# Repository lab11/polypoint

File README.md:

PolyPoint
=========

PolyPoint is a system for using ultra-wideband RF time-of-flight ranging to perform indoor localization.
It incorporates the DecaWave DW1000 for UWB packet transmission and timestamping
into a solder-on module that provides node-to-node ranges over an I2C interface.

Name
----

The name PolyPoint comes from the use of many polygons and shapes in the prototype design and the
desire to pinpoint where users are with the system.

Git Clone
---------

When cloning this repository, be absolutely sure to do

    git clone --recursive https://github.com/lab11/polypoint.git
    
so that you get the submodules as well. All of the supporting
libraries and build tools are in submodules for the various
hardware platforms used in this project.

Hardware
--------

The PolyPoint system is composed of several hardware pieces. At the core is the
TriPoint module which is a 1.25" on a side triangle that encompasses all of the
core ranging hardware and software. TriPoint has castellated edges and can be
soldered on to a carrier board, effectively as a ranging IC. TriTag is one such
carrier board designed to be the tag in the ranging system. It includes the
UWB antennas and a Bluetooth Low Energy radio plus a battery charging circuit.
TriTag is able to provide ranges to a mobile phone application.

### TriPoint

TriPoint includes the following components:

- DecaWave DW1000 UWB radio
- STM32F031G6U6 MCU
- RF switch

The MCU contains all the necessary code to run the DW1000 and the ranging
protocol.

### TriTag

TriTag includes:

- The TriPoint module
- 3 UWB antennas
- nRF51822 BLE radio
- 3.3 V LDO
- Li-ion battery charger

TriTag is designed to be the tag to be localized in the system and connected
to a smartphone.

### TriDev

TriDev is a breakout and testing board for the TriPoint module.
It contains the same BLE hardware as TriTag, but also adds an FTDI
chip for issuing I2C commands over USB.

Software
--------

PolyPoint contains many software layers that run at various levels of
the system.

#### TriPoint

The core firmware that makes the drop-in TriPoint module work
includes all of the logic to implement two way ToF ranging
on top of the DecaWave DW1000 UWB radio. The firmware architecture
supports multiple "applications", or ranging algorithms, that can
be selected at runtime.

#### TriTag

The TriTag code implements a BLE application
that uses the TriPoint module as an I2C device and prov
a BLE service. It puts the TriTag hardware into TAG mode
and provides ranges over a BLE characteristic. 

#### Phone and BLE

The tools in the `/phone` directory interact with TriTag and read data
across the BLE interface.

----

## Academic Publications

The PolyPoint project has led to two academic publications, and an invited talk at HotWireless'16.
If you are interested in the theory behind the ranging protocol, please check out our publications:

 - **[SurePoint: Exploiting Ultra Wideband Flooding and Diversity to Provide Robust, Scalable, High-Fidelity Indoor Localization.](http://lab11.eecs.berkeley.edu/content/pubs/kempke16surepoint.pdf)** Benjamin Kempke, Pat Pannuto, Bradford Campbell, and Prabal Dutta. Proceedings of the 14th ACM Conference on Embedded Networked Sensor Systems (SenSys’16).
 - **[PolyPoint: Guiding Indoor Quadrotors with Ultra-Wideband Localization.](http://lab11.eecs.berkeley.edu/content/pubs/kempke15polypoint.pdf)** Benjamin Kempke, Pat Pannuto, and Prabal Dutta. 2015 ACM Workshop on Hot Topics in Wireless (HotWireless’15).
 
If you use PolyPoint or its derivatives, please use the following citation:

```bibtex
@inproceedings{kempke16surepoint,
	title = {{SurePoint}: Exploiting Ultra Wideband Flooding and Diversity to Provide Robust, Scalable, High-Fidelity Indoor Localization},
	booktitle = {Proceedings of the 14th ACM Conference on Embedded Networked Sensor Systems},
	series = {SenSys'16},
	year = {2016},
	month = {11},
	location = {Stanford, CA, USA},
	conference-url = {http://sensys.acm.org/2016/},
	author = {Kempke, Benjamin and Pannuto, Pat and Campbell, Bradford and Dutta, Prabal},
}
```

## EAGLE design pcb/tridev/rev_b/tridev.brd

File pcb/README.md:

PolyPoint Hardware
==================

The PolyPoint system consists of several PCBs centered around TriPoint,
the core UWB ranging module.

1. **TriPoint**: Triangular module which contains all necessary hardware
for using the DecaWave DW1000. It has castellated headers so it can be
soldered onto a carrier board to add indoor localization functionality
to any device.

2. **TriTag**: Portable carrier board designed to be used as an indoor
localization tag. Has TriPoint on one side and a BLE radio on the other.

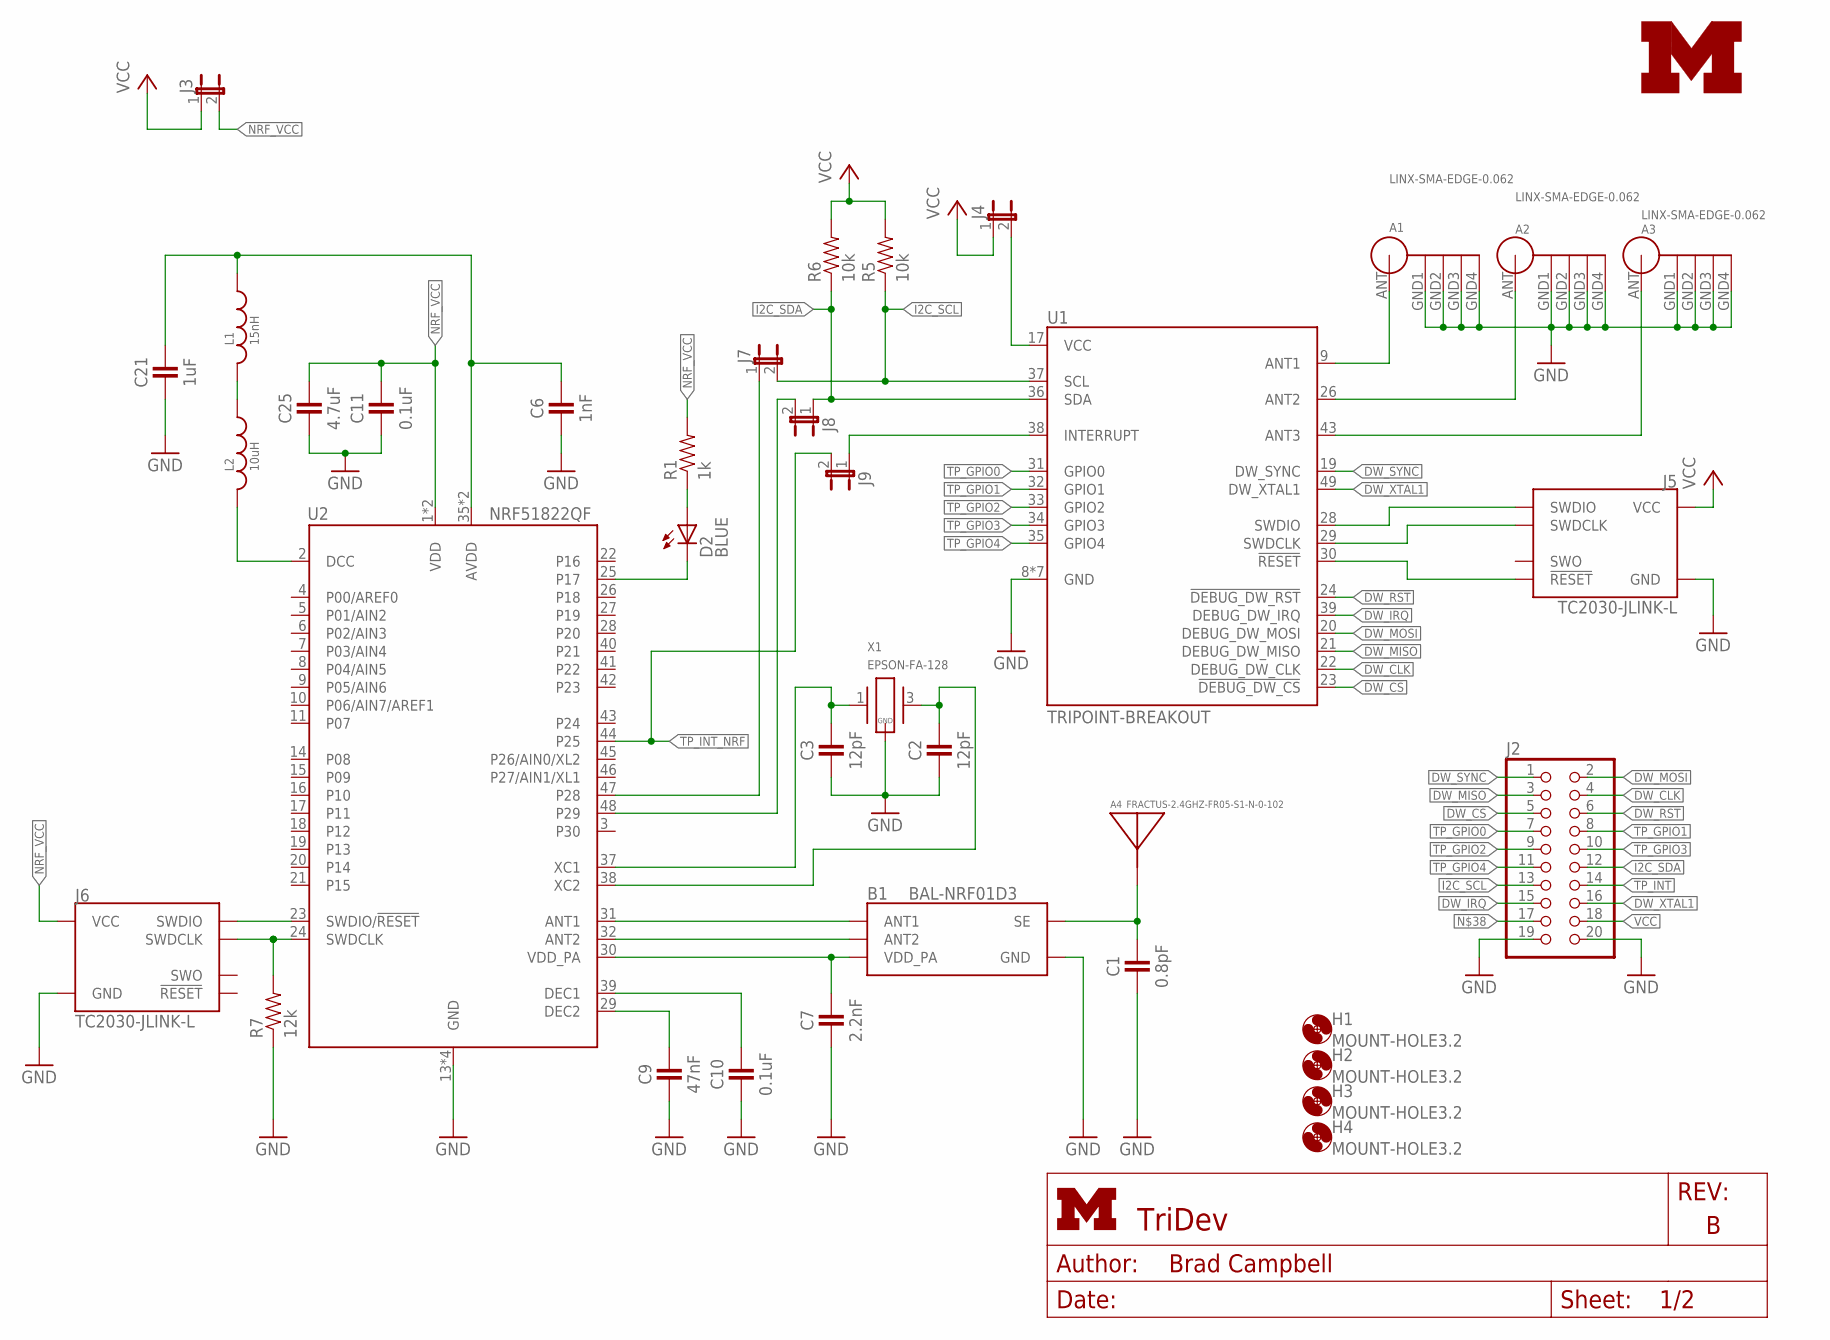
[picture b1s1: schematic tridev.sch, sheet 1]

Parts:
A1, A2, A3: LINX-SMA-EDGE-0.062; CONSMA003.062
A4: FRACTUS-2.4GHZ-FR05-S1-N-0-102; FRACTUS-ANTENNA-FR05-S1-N-0-102
B1: BAL-NRF01D3
C1: 0.8pF; 0402_CAP
C2, C3: 12pF; 0402_CAP
C6: 1nF; 0402_CAP
C7: 2.2nF; 0402_CAP
C9: 47nF; 0402_CAP
C10, C11: 0.1uF; 0402_CAP
C21: 1uF; 0402_CAP
C25: 4.7uF; 0402_CAP
D2: BLUE; LED-0603
H1, H2, H3, H4: MOUNT-HOLE3.2; 3,2
J2: PINHD-2X10; 2X10
J3, J4, J7, J8, J9: JUMPER-2PTH; 1X02
J5, J6: TC2030-JLINK-L; TC2030-IDC
L1: 15nH; 0402_CAP
L2: 10uH; 0603_CAP
LOGO1: UMICH_SOLID_SMALL; UMICH_SOLID_75MIL
R1: 1k; 0402_RES
R5, R6: 10k; 0402_RES
R7: 12k; 0402_RES
U1: TRIPOINT-BREAKOUT
U2: NRF51822QF; QFN-48-6MM
X1: EPSON-FA-128; FA-128

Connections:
!CHRG1: D2.A, R1.1
!DW_CS: J2.5, U1.23 (!DEBUG_DW_CS)
!DW_RST: J2.6, U1.24 (!DEBUG_DW_RST)
ANTENNA: A4.1, B1.SE, C1.1
AVDD: C6.1, C21.1, L1.1, U2.35 (AVDD), U2.36 (AVDD)
DCC: L2.2, U2.2 (DCC)
DW_CLK: J2.4, U1.22 (DEBUG_DW_CLK)
DW_IRQ: J2.15, U1.39 (DEBUG_DW_IRQ)
DW_MISO: J2.3, U1.21 (DEBUG_DW_MISO)
DW_MOSI: J2.2, U1.20 (DEBUG_DW_MOSI)
DW_SYNC: J2.1, U1.19 (DW_SYNC)
DW_XTAL1: J2.16, U1.49 (DW_XTAL1)
GND: A1.GND1, A1.GND2, A1.GND3, A1.GND4, A2.GND1, A2.GND2, A2.GND3, A2.GND4, A3.GND1, A3.GND2, A3.GND3, A3.GND4, B1.GND, C1.2, C2.2, C3.2, C6.2, C7.2, C9.2, C10.2, C11.2, C21.2, C25.2, J2.19, J2.20, J5.5 (GND), J6.5 (GND), R7.1, U1.8 (GND), U1.10 (GND), U1.18 (GND), U1.25 (GND), U1.27 (GND), U1.42 (GND), U1.44 (GND), U2.13 (GND), U2.33 (GND), U2.34 (GND), U2.GND, X1.2 (GND), X1.4 (GND); also elsewhere on the board
I2C_SCL: J2.13, J7.2, R5.1, U1.37 (SCL); also elsewhere on the board
I2C_SCL_NRF: J7.1, U2.47 (P28)
I2C_SDA: J2.12, J8.1, R6.1, U1.36 (SDA); also elsewhere on the board
I2C_SDA_NRF: J8.2, U2.48 (P29)
unnamed: A1.ANT, U1.9 (ANT1)
unnamed: A2.ANT, U1.26 (ANT2)
unnamed: A3.ANT, U1.43 (ANT3)
unnamed: J5.2 (SWDIO), U1.28 (SWDIO)
unnamed: D2.C, U2.25 (P17)
unnamed: J5.4 (SWDCLK), U1.29 (SWDCLK)
unnamed: J5.3 (!RESET), U1.30 (!RESET)
unnamed: C3.1, U2.37 (XC1), X1.1
unnamed: C2.1, U2.38 (XC2), X1.3 (2)
unnamed: C9.1, U2.29 (DEC2)
unnamed: C10.1, U2.39 (DEC1)
unnamed: B1.ANT1, U2.31 (ANT1)
unnamed: B1.ANT2, U2.32 (ANT2)
unnamed: B1.VCC (VDD_PA), C7.1, U2.30 (VDD_PA)
unnamed: J4.2, U1.17 (VCC)
unnamed: L1.2, L2.1
NRF_VCC: C11.1, C25.1, J3.2, J6.1 (VCC), R1.2, U2.1 (VDD), U2.12 (VDD)
SWDCLK: J6.4 (SWDCLK), R7.2, U2.24 (SWDCLK)
SWDIO/!RESET: J6.2 (SWDIO), U2.23 (SWDIO/!RESET)
TP_GPIO0: J2.7, U1.31 (GPIO0)
TP_GPIO1: J2.8, U1.32 (GPIO1)
TP_GPIO2: J2.9, U1.33 (GPIO2)
TP_GPIO3: J2.10, U1.34 (GPIO3)
TP_GPIO4: J2.11, U1.35 (GPIO4)
TP_INT: J2.14, J9.1, U1.38 (INTERRUPT); also elsewhere on the board
TP_INT_NRF: J9.2, U2.44 (P25)
VCC: J2.18, J3.1, J4.1, J5.1 (VCC), R5.2, R6.2; also elsewhere on the board

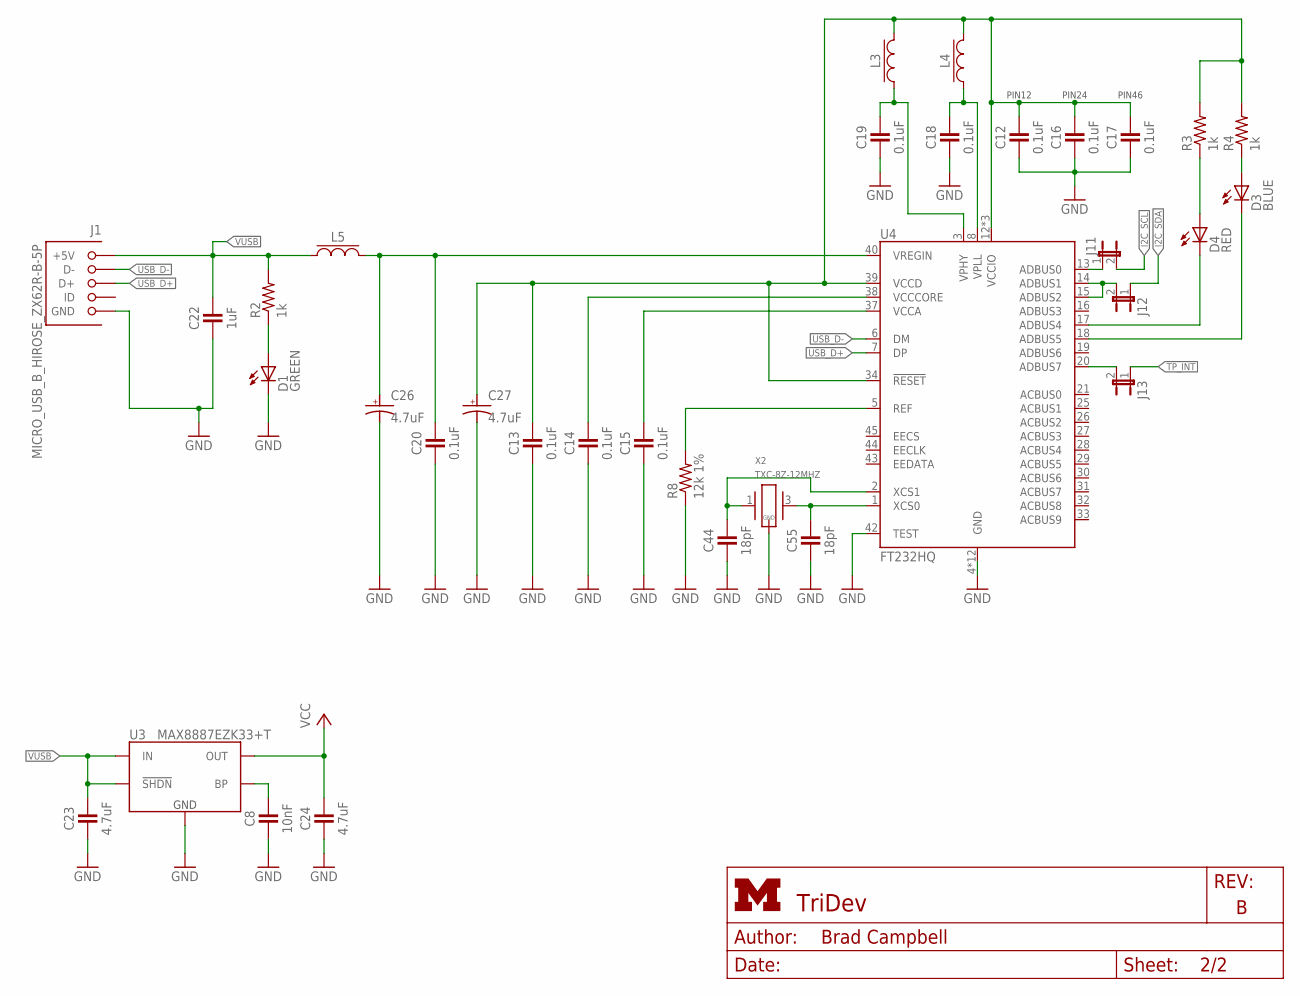
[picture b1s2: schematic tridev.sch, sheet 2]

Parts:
C8: 10nF; 0402_CAP
C12, C13, C14, C15, C16, C17, C18, C19, C20: 0.1uF; 0402_CAP
C22: 1uF; 0402_CAP
C23, C24: 4.7uF; 0402_CAP
C26, C27: 4.7uF; CAP0603; DIGIKEY 478-8656-1-ND
C44, C55: 18pF; 0402_CAP
D1: GREEN; LED-0603
D3: BLUE; LED-0603
D4: RED; LED-0603
J1: MICRO_USB_B_HIROSE_ZX62R-B-5P; USB_MICRO_B-HIROSE-ZX62R-B-5P; MOUSER 798-ZX62R-B-5P
J11, J12, J13: JUMPER-2PTH; 1X02
L3, L4, L5: FERRITE_BEAD; 0603_CAP; DIGIKEY 445-2166-1-ND
R2, R3, R4: 1k; 0402_RES
R8: 12k 1%; 0402_RES
U3: MAX8887EZK33+T; SOT-23-5
U4: FT232HQ; QFN-48-8MM
X2: TXC-8Z-12MHZ; TXC-8Z

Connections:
!CHRG: D1.A, R2.1
GND: C8.2, C12.2, C13.2, C14.2, C15.2, C16.2, C17.2, C18.2, C19.2, C20.2, C22.2, C23.2, C24.2, C26.NEG (ANODE), C27.NEG (ANODE), C44.2, C55.2, D1.C, J1.5 (GND), R8.1, U3.2 (GND), U4.4 (GND), U4.9 (GND), U4.10 (GND), U4.11 (GND), U4.22 (GND), U4.23 (GND), U4.35 (GND), U4.36 (GND), U4.41 (GND), U4.42 (TEST), U4.47 (GND), U4.48 (GND), U4.PAD (GND), X2.2 (GND), X2.4 (GND); also elsewhere on the board
I2C_SCL: J11.2; also elsewhere on the board
I2C_SCL_FTDI: J11.1, U4.13 (ADBUS0)
I2C_SDA: J12.1; also elsewhere on the board
I2C_SDA_FTDI: J12.2, U4.14 (ADBUS1), U4.15 (ADBUS2)
unnamed: D4.C, U4.17 (ADBUS4)
unnamed: C8.1, U3.4 (BP)
unnamed: C20.1, C26.POS (CATHODE), L5.2, U4.40 (VREGIN)
unnamed: C14.1, U4.38 (VCCCORE)
unnamed: C55.1, U4.1 (XCS0), X2.3 (2)
unnamed: C44.1, U4.2 (XCS1), X2.1
unnamed: C15.1, U4.37 (VCCA)
unnamed: R8.2, U4.5 (REF)
unnamed: D4.A, R3.1
unnamed: D3.A, R4.1
unnamed: D3.C, U4.18 (ADBUS5)
TP_INT: J13.1; also elsewhere on the board
TP_INT_FTDI: J13.2, U4.20 (ADBUS7)
USB_D+: J1.3 (D+), U4.7 (DP)
USB_D-: J1.2 (D-), U4.6 (DM)
VCC: C24.1, U3.5 (OUT); also elsewhere on the board
VCC3V3: C12.1, C13.1, C16.1, C17.1, C27.POS (CATHODE), L3.2, L4.2, R3.2, R4.2, U4.12 (VCCIO), U4.24 (VCCIO), U4.34 (!RESET), U4.39 (VCCD), U4.46 (VCCIO)
VPHY: C19.1, L3.1, U4.3 (VPHY)
VPLL: C18.1, L4.1, U4.8 (VPLL)
VUSB: C22.1, C23.1, J1.1 (+5V), L5.1, R2.2, U3.1 (IN), U3.3 (!SHDN)

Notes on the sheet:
PIN12
PIN24
PIN46

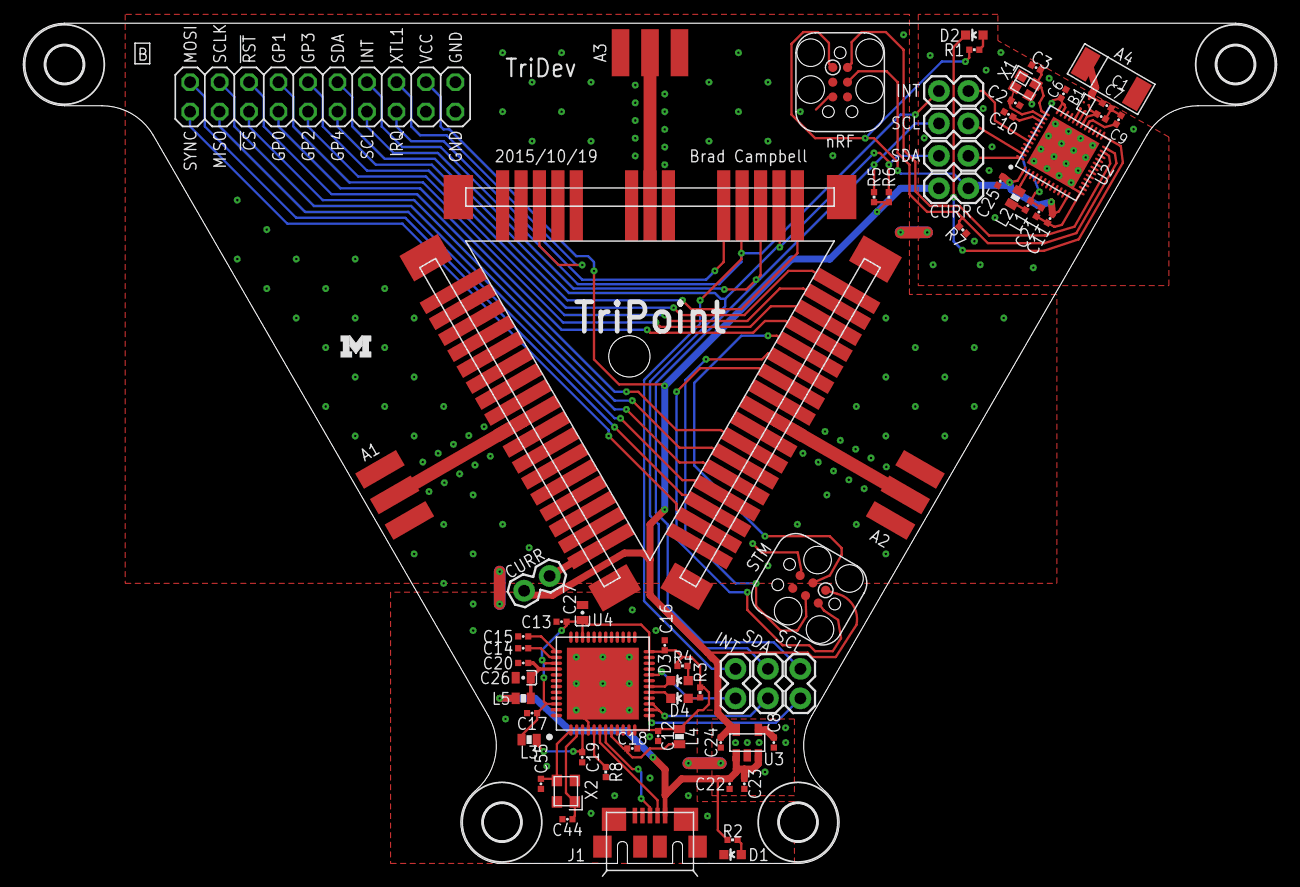
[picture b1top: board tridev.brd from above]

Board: 2 copper layers, 108.0 x 72.4 mm, 72 parts (0 on the bottom side), 65 nets.

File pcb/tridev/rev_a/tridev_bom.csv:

Qty,Value,Device,Package,Parts,Description,DIGIKEY,MOUSER,NEWARK,RICHARDSON_RFPD,
3,LINX-SMA-EDGE-0.062,LINX-SMA-EDGE-0.062,CONSMA003.062,"A1, A2, A3",CONN SMA JACK 50 OHM EDGE MNT,CONSMA003.062-ND,,,,y
1,FRACTUS-2.4GHZ-FR05-S1-N-0-102,FRACTUS-2.4GHZ-FR05-S1-N-0-102,FRACTUS-ANTENNA-FR05-S1-N-0-102,A4,"Fractus Compact Reach XtendTM chip antenna is engineered specifically for Bluetooth,",,,,FR05-S1-N-0102B,y
1,BAL-NRF01D3,BAL-NRF01D3,BAL-NRF01D3,B1,"50 ohm nominal input / conjugate match balun to nRF51422-QFAA,",497-13637-1-ND,511-BAL-NRF01D3,,,y
1,0.8pF,CAPACITOR,0402_CAP,C1,0402 Capacitor,490-6269-1-ND,,,,y
2,12pF,CAPACITOR,0402_CAP,"C2, C3",0402 Capacitor,490-6197-1-ND,,,,y
2,18pF,CAPACITOR,0402_CAP,"C4, C5",0402 Capacitor,490-6203-1-ND,,,,y
1,1nF,CAPACITOR,0402_CAP,C6,0402 Capacitor,490-1303-1-ND,,,,y
1,2.2nF,CAPACITOR,0402_CAP,C7,0402 Capacitor,490-5419-1-ND,,,,y
1,10nF,CAPACITOR,0402_CAP,C8,0402 Capacitor,445-1260-1-ND,,,,y
1,47nF,CAPACITOR,0402_CAP,C9,0402 Capacitor,445-1264-1-ND,,,,y
11,0.1uF,CAPACITOR,0402_CAP,C10-C20,0402 Capacitor,490-1318-1-ND,,,,y
2,1uF,CAPACITOR,0402_CAP,"C21, C22",0402 Capacitor,445-4998-1-ND,,,,y
3,4.7uF,CAPACITOR,0402_CAP,"C23, C24, C25",0402 Capacitor,445-5947-1-ND,,,,y
2,4.7uF,CAP_POL0603,CAP0603,"C26, C27",0603 Capacitor,478-8656-1-ND,,,,y
1,GREEN,LED0603,LED-0603,D1,LEDs,160-1446-1-ND,,,,y
2,BLUE,LED0603,LED-0603,"D2, D3",LEDs,160-1837-1-ND,,,,y
1,RED,LED0603,LED-0603,D4,LEDs,160-1835-1-ND,,,,y
1,MICRO_USB_B_HIROSE_ZX62R-B-5P,MICRO_USB_B_HIROSE_ZX62R-B-5P,USB_MICRO_B-HIROSE-ZX62R-B-5P,J1,USB Micro B Connector,H11574CT-ND,798-ZX62R-B-5P,69W0714,,y
1,,PINHD-2X10,2X10,J2,PIN HEADER,609-3365-ND,,,,y
2,,JUMPER-2PTH,1X02,"J3, J4",Jumper,,,,,y
1,15nH,INDUCTOR0402,0402_CAP,L1,,587-1521-1-ND,,,,y
1,10uH,INDUCTOR0603,0603_CAP,L2,,490-4025-1-ND,,,,y
3,FERRITE_BEAD,FERRITE_BEAD,0603_CAP,"L3, L4, L5",,445-2166-1-ND,,,,y
4,1k,RESISTOR0402_RES,0402_RES,"R1, R2, R3, R4",Resistor,RHM1.0KCECT-ND,,,,y
2,10k,RESISTOR0402_RES,0402_RES,"R5, R6",Resistor,RHM10.0KCDCT-ND,,,,y
1,12k 1%,RESISTOR0402_RES,0402_RES,"R7, R8",Resistor,RHM12.0KCDCT-ND,,,,y
1,TRIPOINT-BREAKOUT,TRIPOINT-BREAKOUT,TRIPOINT-BREAKOUT,U1,UWB Ranging Module,,,,,y
1,NRF51822QF,NRF51822QF,QFN-48-6MM,U2,Multiprotocol Bluetooth® 4.0 low energy/2.4 GHz RF SoC,1490-1032-1-ND,949-NRF51822-QFAB-R7,,,y
1,MAX8887EZK33+T,MAX8887EZK33+T,SOT-23-5,U3,IC REG LDO 3.3V 0.3A TSOT23-5,MAX8887EZK33+TCT-ND,,,,y
1,FT232HQ,FT232HQ,QFN-48-8MM,U4,Single Channel USB to Multipurpose I/O IC,768-1102-1-ND,895-FT232HQ-REEL,65W8039,,y
1,16MHz,TXC-8Y,TXC-8Y,X1,CRYSTAL 16MHZ 8PF SMD,887-2003-1-ND,,,,y
1,TXC-8Z-12MHZ,TXC-8Z-12MHZ,TXC-8Z,X2,,887-1487-1-ND,,,,y

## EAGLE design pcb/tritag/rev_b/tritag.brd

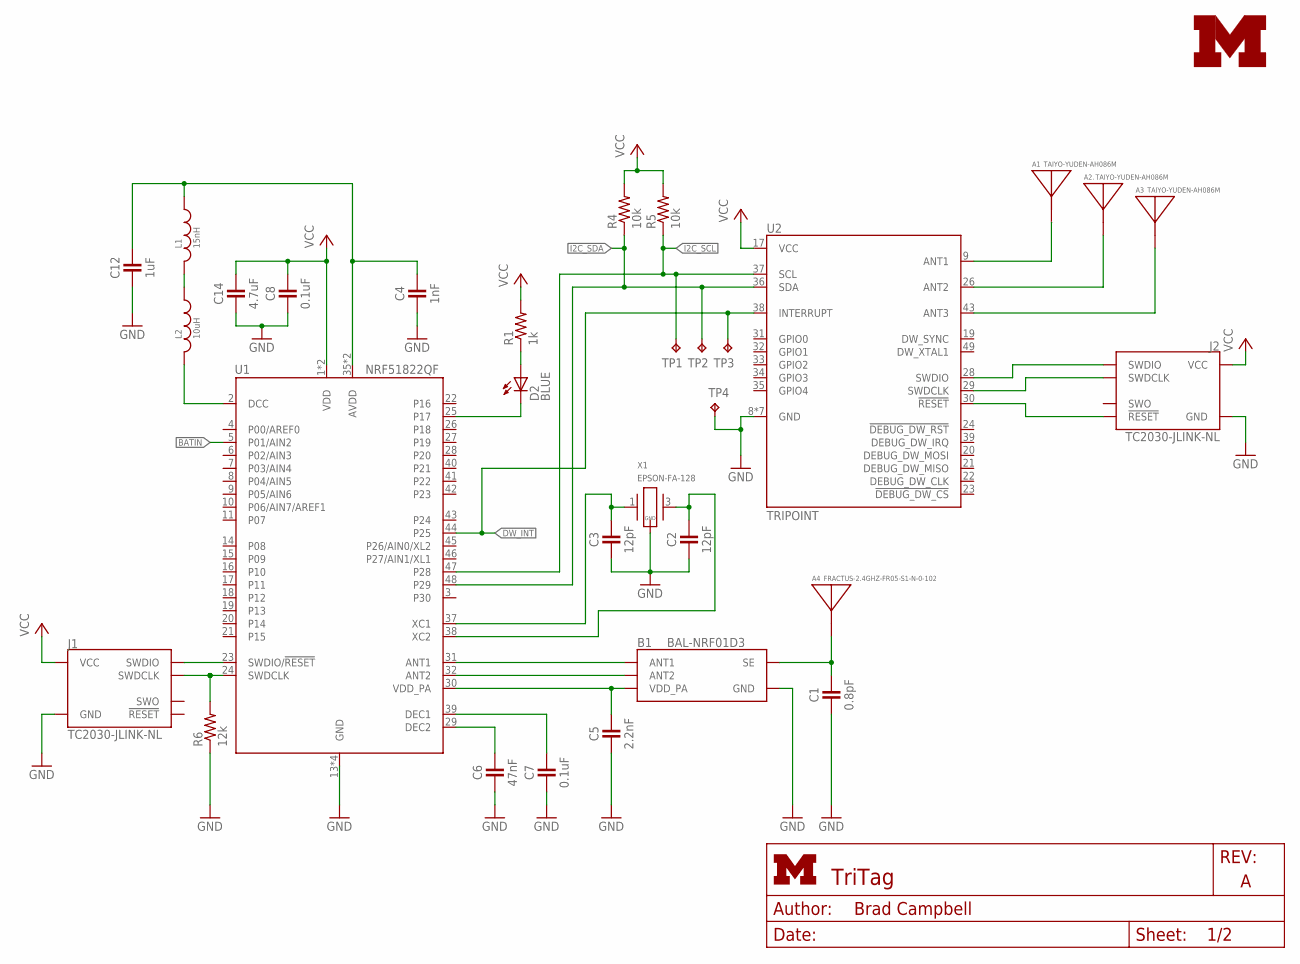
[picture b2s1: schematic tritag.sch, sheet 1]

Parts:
A1, A2., A3: TAIYO-YUDEN-AH086M
A4: FRACTUS-2.4GHZ-FR05-S1-N-0-102; FRACTUS-ANTENNA-FR05-S1-N-0-102
B1: BAL-NRF01D3
C1: 0.8pF; 0402_CAP
C2, C3: 12pF; 0402_CAP
C4: 1nF; 0402_CAP
C5: 2.2nF; 0402_CAP
C6: 47nF; 0402_CAP
C7, C8: 0.1uF; 0402_CAP
C12: 1uF; 0402_CAP
C14: 4.7uF; 0402_CAP
D2: BLUE; LED-0603
J1, J2: TC2030-JLINK-NL; TC2030-IDC-NL
L1: 15nH; 0402_CAP
L2: 10uH; 0603_CAP
LOGO1: UMICH_SOLID_SMALL; UMICH_SOLID_75MIL
R1: 1k; 0402_RES
R4, R5: 10k; 0402_RES
R6: 12k; 0402_RES
TP1, TP2, TP3, TP4: TPTP06SQ; TP06SQ
U1: NRF51822QF; QFN-48-6MM
U2: TRIPOINT
X1: EPSON-FA-128; FA-128

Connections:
!CHRG1: D2.A, R1.1
ANTENNA: A4.1, B1.SE, C1.1
AVDD: C4.1, C12.1, L1.1, U1.35 (AVDD), U1.36 (AVDD)
BATIN: U1.5 (P01/AIN2); also elsewhere on the board
DCC: L2.2, U1.2 (DCC)
DW_INT: TP3.TP, U1.44 (P25), U2.38 (INTERRUPT)
GND: B1.GND, C1.2, C2.2, C3.2, C4.2, C5.2, C6.2, C7.2, C8.2, C12.2, C14.2, J1.5 (GND), J2.5 (GND), R6.1, TP4.TP, U1.13 (GND), U1.33 (GND), U1.34 (GND), U1.GND, U2.8 (GND), U2.10 (GND), U2.18 (GND), U2.25 (GND), U2.27 (GND), U2.42 (GND), U2.44 (GND), X1.2 (GND), X1.4 (GND); also elsewhere on the board
I2C_SCL: R5.1, TP1.TP, U1.47 (P28), U2.37 (SCL)
I2C_SDA: R4.1, TP2.TP, U1.48 (P29), U2.36 (SDA)
unnamed: A1.A, U2.9 (ANT1)
unnamed: A2..A, U2.26 (ANT2)
unnamed: A3.A, U2.43 (ANT3)
unnamed: J2.2 (SWDIO), U2.28 (SWDIO)
unnamed: D2.C, U1.25 (P17)
unnamed: J2.4 (SWDCLK), U2.29 (SWDCLK)
unnamed: J2.3 (!RESET), U2.30 (!RESET)
unnamed: C3.1, U1.37 (XC1), X1.1
unnamed: C2.1, U1.38 (XC2), X1.3 (2)
unnamed: C6.1, U1.29 (DEC2)
unnamed: C7.1, U1.39 (DEC1)
unnamed: B1.ANT1, U1.31 (ANT1)
unnamed: B1.ANT2, U1.32 (ANT2)
unnamed: B1.VCC (VDD_PA), C5.1, U1.30 (VDD_PA)
unnamed: L1.2, L2.1
SWDCLK: J1.4 (SWDCLK), R6.2, U1.24 (SWDCLK)
SWDIO/!RESET: J1.2 (SWDIO), U1.23 (SWDIO/!RESET)
VCC: C8.1, C14.1, J1.1 (VCC), J2.1 (VCC), R1.2, R4.2, R5.2, U1.1 (VDD), U1.12 (VDD), U2.17 (VCC); also elsewhere on the board

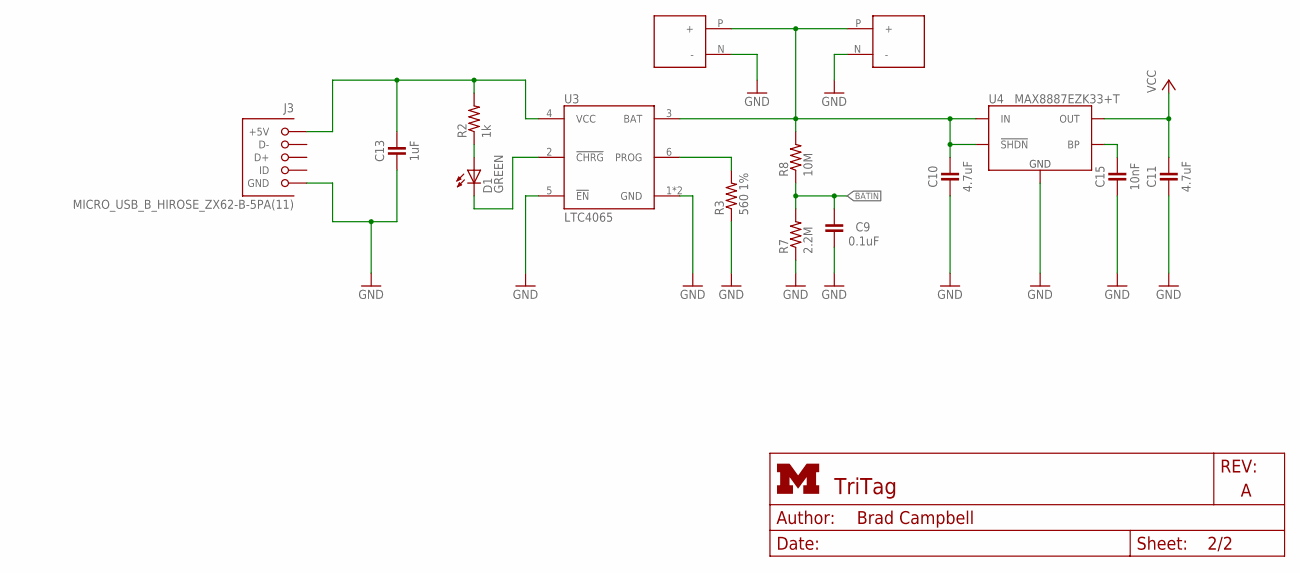
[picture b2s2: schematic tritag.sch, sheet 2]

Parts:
C9: 0.1uF; 0402_CAP
C10, C11: 4.7uF; 0402_CAP
C13: 1uF; 0402_CAP
C15: 10nF; 0402_CAP
D1: GREEN; LED-0603
J3: MICRO_USB_B_HIROSE_ZX62-B-5PA(11); USB_MICRO_B-HIROSE-ZX62-B-5PA(11)
J4, J5: BAT_HOLE; BATTERY_HOLE
R2: 1k; 0402_RES
R3: 560 1%; 0402_RES
R7: 2.2M; 0402_RES
R8: 10M; 0402_RES
U3: LTC4065; DFN-6/2MM
U4: MAX8887EZK33+T; SOT-23-5

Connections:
!CHRG: D1.A, R2.1
BATIN: C9.2, R7.2, R8.1; also elsewhere on the board
GND: C9.1, C10.2, C11.2, C13.2, C15.2, J3.5 (GND), J4.N (-), J5.N (-), R3.1, R7.1, U3.1 (GND), U3.5 (!EN), U3.7 (GND), U4.2 (GND); also elsewhere on the board
unnamed: D1.C, U3.2 (!CHRG)
unnamed: C15.1, U4.4 (BP)
unnamed: R3.2, U3.6 (PROG)
VBAT: C10.1, J4.P (+), J5.P (+), R8.2, U3.3 (BAT), U4.1 (IN), U4.3 (!SHDN)
VCC: C11.1, U4.5 (OUT); also elsewhere on the board
VUSB: C13.1, J3.1 (+5V), R2.2, U3.4 (VCC)

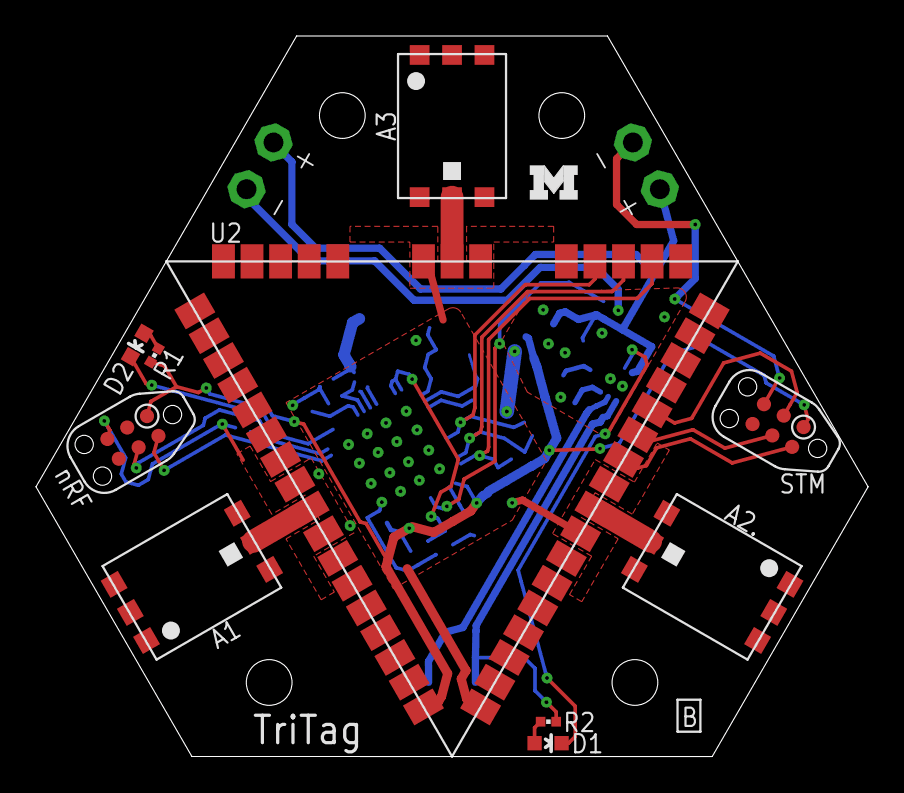
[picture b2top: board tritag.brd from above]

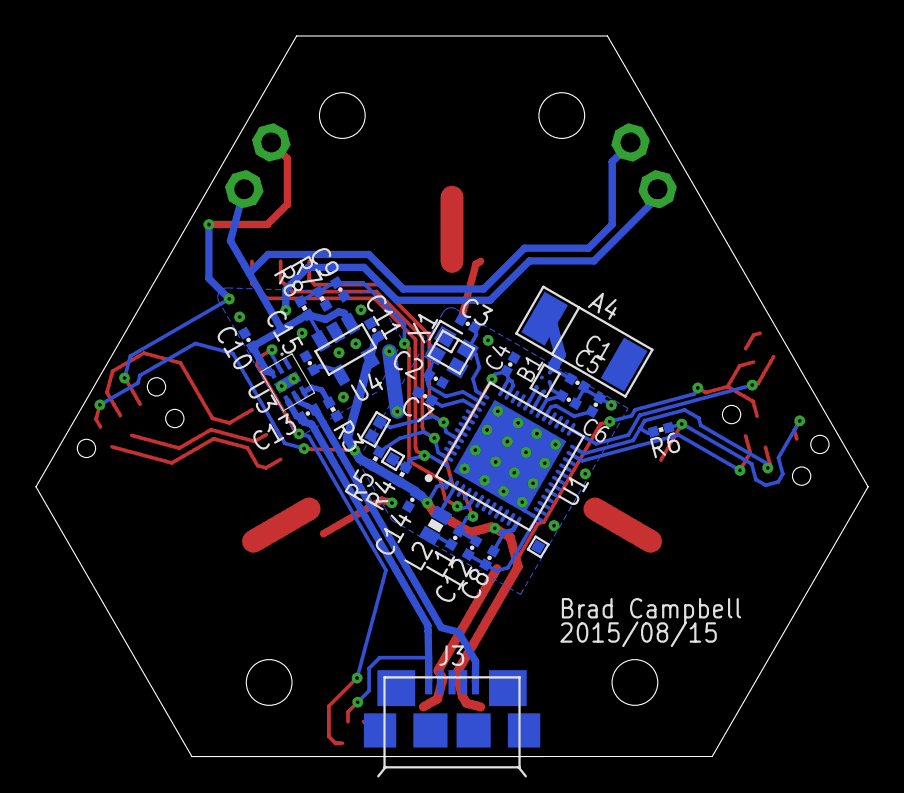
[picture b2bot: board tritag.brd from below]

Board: 2 copper layers, 46.2 x 40.0 mm, 47 parts (34 on the bottom side), 33 nets.

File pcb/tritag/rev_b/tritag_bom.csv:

Qty,Value,Device,Package,Parts,Description,DIGIKEY,MOUSER,NEWARK,RICHARDSON_RFPD
3,TAIYO-YUDEN-AH086M,TAIYO-YUDEN-AH086M,TAIYO-YUDEN-AH086M,"A1, A2, A3",UWB Antenna - 3.1-8GHz,587-2204-1-ND,,,
1,FRACTUS-2.4GHZ-FR05-S1-N-0-102,FRACTUS-2.4GHZ-FR05-S1-N-0-102,FRACTUS-ANTENNA-FR05-S1-N-0-102,A4,"Fractus Compact Reach XtendTM chip antenna is engineered specifically for Bluetooth,",,,,FR05-S1-N-0102B
1,BAL-NRF01D3,BAL-NRF01D3,BAL-NRF01D3,B1,"50 ohm nominal input / conjugate match balun to nRF51422-QFAA,",497-13637-1-ND,511-BAL-NRF01D3,,
1,0.8pF,CAPACITOR,0402_CAP,C1,0402 Capacitor,490-6269-1-ND,,,
2,12pF,CAPACITOR,0402_CAP,"C2, C3",0402 Capacitor,490-6197-1-ND,,,
1,1nF,CAPACITOR,0402_CAP,C4,0402 Capacitor,490-1303-1-ND,,,
1,2.2nF,CAPACITOR,0402_CAP,C5,0402 Capacitor,490-5419-1-ND,,,
1,10nF,CAPACITOR,0402_CAP,C15,0402 Capacitor,445-1260-1-ND,,,
1,47nF,CAPACITOR,0402_CAP,C6,0402 Capacitor,445-1264-1-ND,,,
3,0.1uF,CAPACITOR,0402_CAP,"C7, C8, C9",0402 Capacitor,490-1318-1-ND,,,
2,1uF,CAPACITOR,0402_CAP,"C12, C13",0402 Capacitor,445-4998-1-ND,,,
3,4.7uF,CAPACITOR,0402_CAP,"C10, C11, C14",0402 Capacitor,445-5947-1-ND,,,
1,GREEN,LED0603,LED-0603,D1,LEDs,160-1446-1-ND,,,
1,BLUE,LED0603,LED-0603,D2,LEDs,160-1837-1-ND,,,
1,MICRO_USB_B_HIROSE_ZX62-B-5PA(11),MICRO_USB_B_HIROSE_ZX62-B-5PA(11),USB_MICRO_B-HIROSE-ZX62-B-5PA(11),J3,"Connector Receptacle USB - micro B 2.0 5 Position Surface Mount, Right Angle, Horizontal",H11634CT-ND,798-ZX62-B-5PA11,86P8793,
1,15nH,INDUCTOR0402,0402_CAP,L1,INDUCTOR HI FREQ 15NH 5% 0402,587-1521-1-ND,,,
1,10uH,INDUCTOR0603,0603_CAP,L2,INDUCTOR 10UH 50MA 0603,490-4025-1-ND,,,
2,1k,RESISTOR0402_RES,0402_RES,"R1, R2",Resistor,RHM1.0KCECT-ND,,,
1,2k 1%,RESISTOR0402_RES,0402_RES,R3,Resistor,RHM2KCDCT-ND,,,
2,10k,RESISTOR0402_RES,0402_RES,"R4, R5",Resistor,RHM10.0KCDCT-ND,,,
1,12k,RESISTOR0402_RES,0402_RES,R6,Resistor,RHM12.0KCDCT-ND,,,
1,2.2M,RESISTOR0402_RES,0402_RES,R7,Resistor,541-2.20MLCT-ND,,,
1,10M,RESISTOR0402_RES,0402_RES,R8,Resistor,RHM10MBICT-ND,,,
1,NRF51822QF,NRF51822QF,QFN-48-6MM,U1,Multiprotocol Bluetooth® 4.0 low energy/2.4 GHz RF SoC,1490-1042-1-ND,949-NRF51822-QFAB-R7,,
1,TRIPOINT,TRIPOINT,TRIPOINT,U2,UWB Ranging Module,,,,
1,LTC4065,LTC4065,DFN-6/2MM,U3,LION/LIPO Battery Charging IC Low current,LTC4065LEDC#TRMPBFCT-ND,,,
1,MAX8887EZK33+T,MAX8887EZK33+T,SOT-23-5,U4,IC REG LDO 3.3V 0.3A TSOT23-5,MAX8887EZK33+TCT-ND,,,
1,16MHz,TXC-8Y,TXC-8Y,X1,CRYSTAL 16MHZ 8PF SMD,887-2003-1-ND,,,

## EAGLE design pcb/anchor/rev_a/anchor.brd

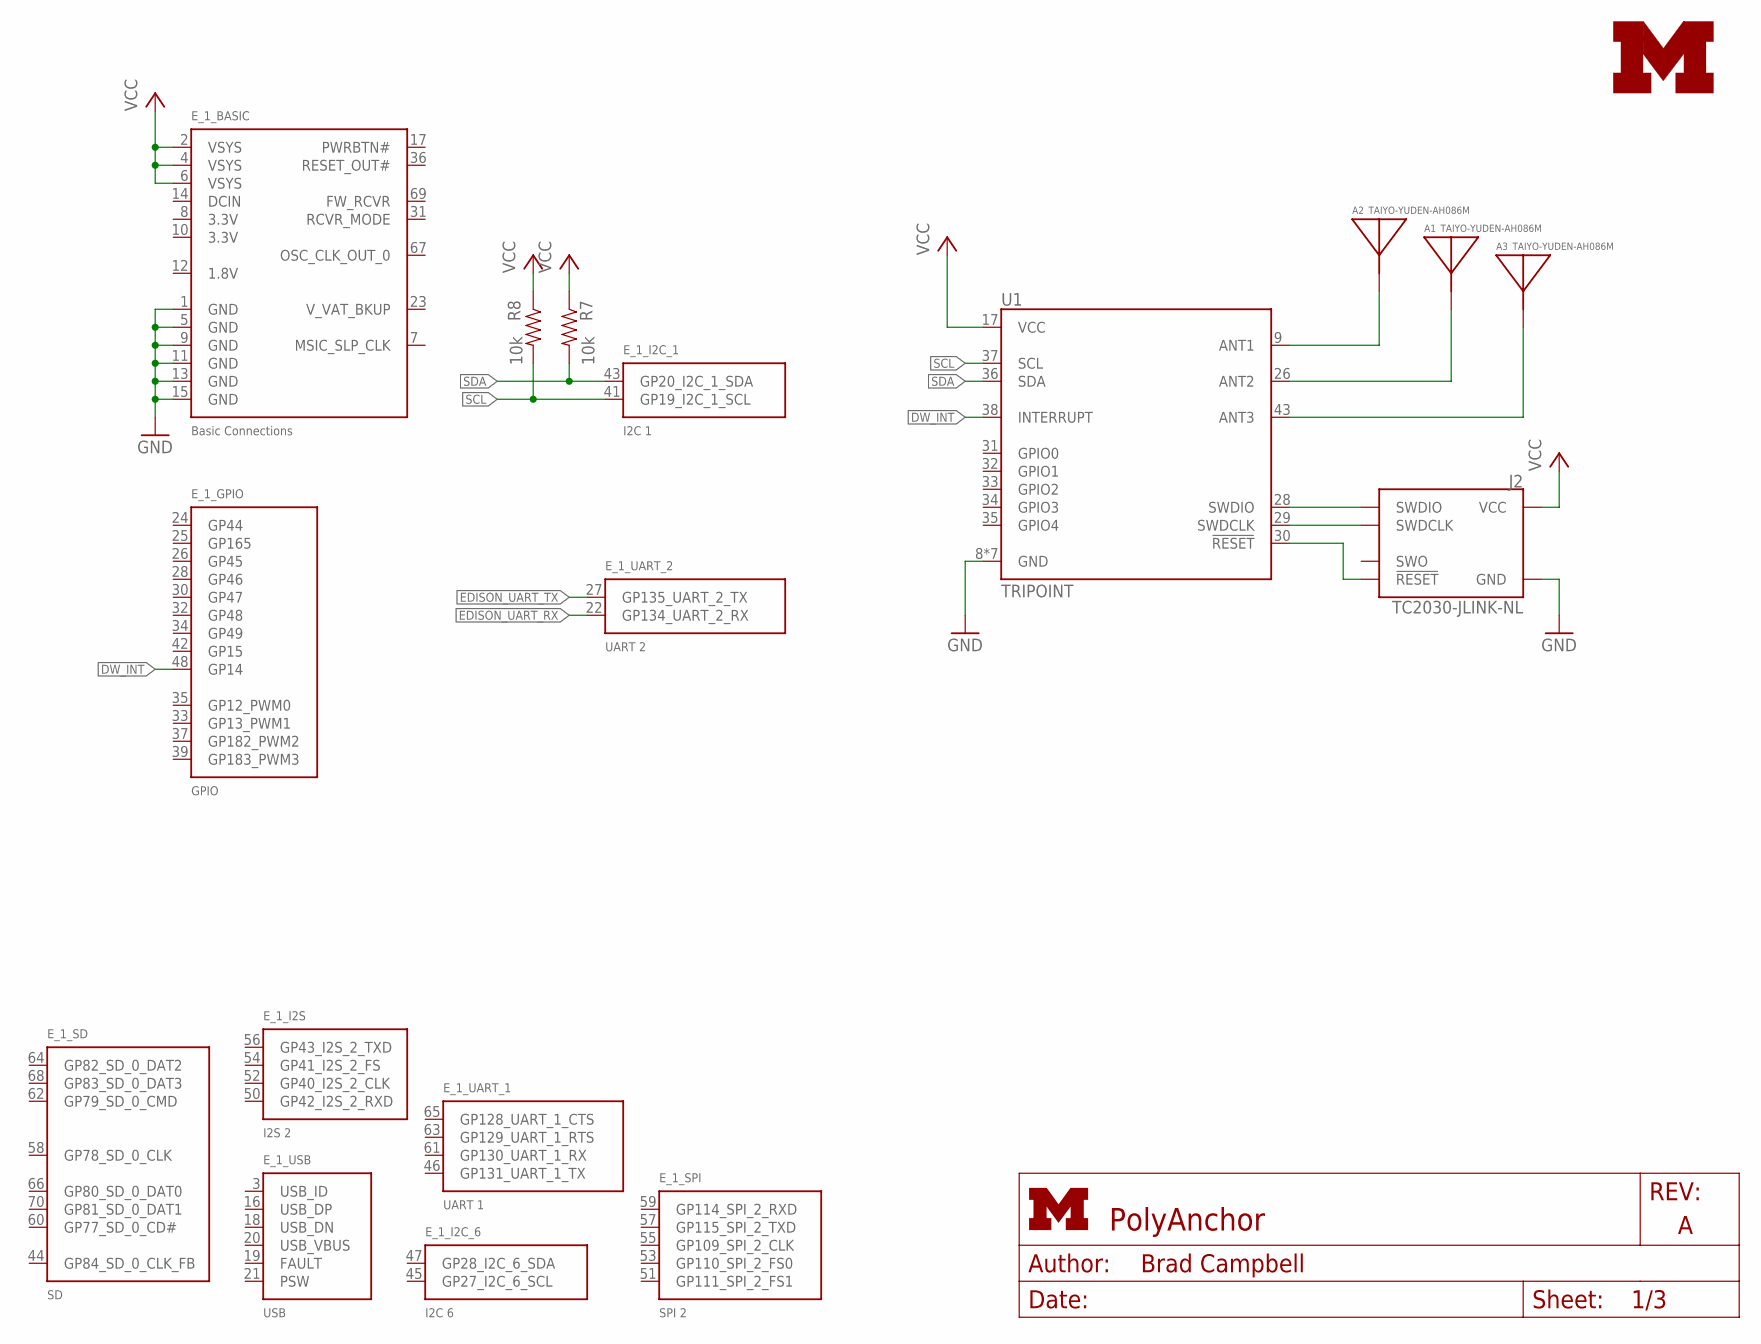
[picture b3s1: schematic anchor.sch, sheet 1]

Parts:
A1, A2, A3: TAIYO-YUDEN-AH086M
E_1: EDISON_CONNECTOR_SEGMENTED; EDISON_DAUGHTER
J2: TC2030-JLINK-NL; TC2030-IDC-NL
LOGO1: UMICH_SOLID_MEDIUM; UMICH_SOLID_200MIL
R7, R8: 10k; 0402_RES
U1: TRIPOINT

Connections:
DW_INT: E_1.48 (GP14), U1.38 (INTERRUPT)
EDISON_UART_RX: E_1.22 (GP134_UART_2_RX); also elsewhere on the board
EDISON_UART_TX: E_1.27 (GP135_UART_2_TX); also elsewhere on the board
GND: E_1.1 (GND), E_1.5 (GND), E_1.9 (GND), E_1.11 (GND), E_1.13 (GND), E_1.15 (GND), J2.5 (GND), U1.8 (GND), U1.10 (GND), U1.18 (GND), U1.25 (GND), U1.27 (GND), U1.42 (GND), U1.44 (GND); also elsewhere on the board
unnamed: J2.2 (SWDIO), U1.28 (SWDIO)
unnamed: A2.A, U1.9 (ANT1)
unnamed: A1.A, U1.26 (ANT2)
unnamed: A3.A, U1.43 (ANT3)
unnamed: J2.4 (SWDCLK), U1.29 (SWDCLK)
unnamed: J2.3 (!RESET), U1.30 (!RESET)
SCL: E_1.41 (GP19_I2C_1_SCL), R8.2, U1.37 (SCL)
SDA: E_1.43 (GP20_I2C_1_SDA), R7.2, U1.36 (SDA)
VCC: E_1.2 (VSYS), E_1.4 (VSYS), E_1.6 (VSYS), J2.1 (VCC), R7.1, R8.1, U1.17 (VCC); also elsewhere on the board

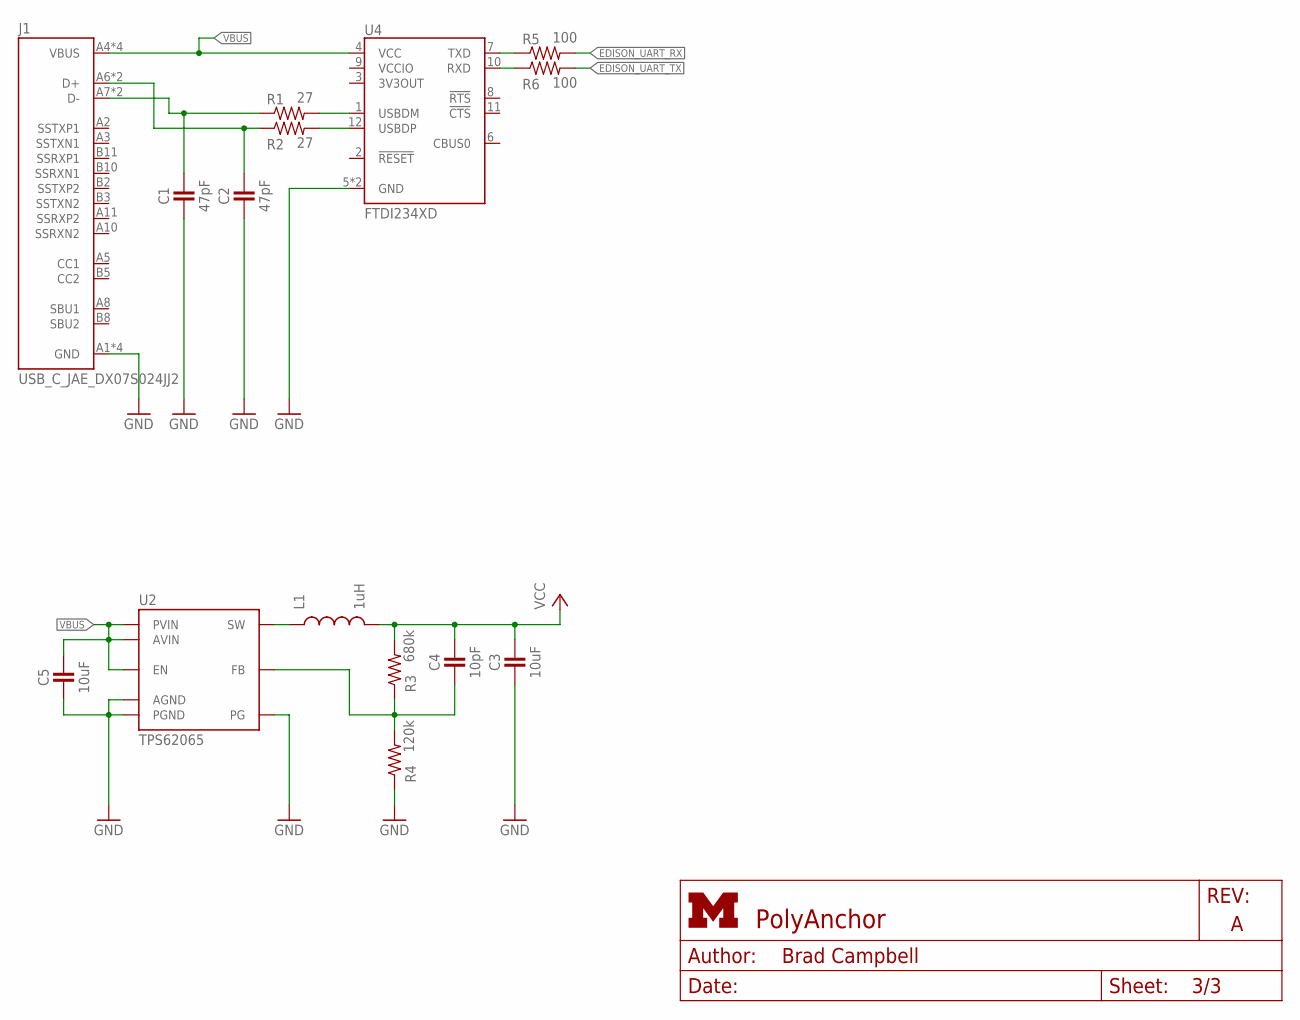
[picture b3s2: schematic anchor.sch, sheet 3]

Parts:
C1, C2: 47pF; 0402_CAP
C3, C5: 10uF; 0603_CAP; DIGIKEY 490-6405-1-ND
C4: 10pF; 0402_CAP
J1: USB_C_JAE_DX07S024JJ2; DX07S024JJ2
L1: 1uH; 1210; DIGIKEY 490-10767-1-ND
R1, R2: 27; 0402_RES
R3: 680k; 0402_RES
R4: 120k; 0402_RES
R5, R6: 100; 0402_RES
U2: TPS62065; S-PWSON-N8
U4: FTDI234XD; DFN-12/3MM

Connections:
D+: C2.1, J1.A6 (D+), J1.B6 (D+), R2.1
D-: C1.1, J1.A7 (D-), J1.B7 (D-), R1.1
EDISON_UART_RX: R5.2; also elsewhere on the board
EDISON_UART_TX: R6.2; also elsewhere on the board
GND: C1.2, C2.2, C3.2, C5.2, J1.A1 (GND), J1.A12 (GND), J1.B1 (GND), J1.B12 (GND), R4.1, U2.1 (PGND), U2.3 (AGND), U2.6 (PG), U2.P$1 (PGND), U4.5 (GND), U4.13 (GND); also elsewhere on the board
unnamed: L1.1, U2.2 (SW)
unnamed: R5.1, U4.7 (TXD)
unnamed: R1.2, U4.1 (USBDM)
unnamed: R2.2, U4.12 (USBDP)
unnamed: C4.2, R3.1, R4.2, U2.4 (FB)
unnamed: R6.1, U4.10 (RXD)
VBUS: C5.1, J1.A4 (VBUS), J1.A9 (VBUS), J1.B4 (VBUS), J1.B9 (VBUS), U2.5 (EN), U2.7 (AVIN), U2.8 (PVIN), U4.4 (VCC)
VCC: C3.1, C4.1, L1.2, R3.2; also elsewhere on the board

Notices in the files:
parts and their libraries:
SparkFun-Passives: Licensing: CC v3.0 Share-Alike You are welcome to use this library for commercial purposes.
